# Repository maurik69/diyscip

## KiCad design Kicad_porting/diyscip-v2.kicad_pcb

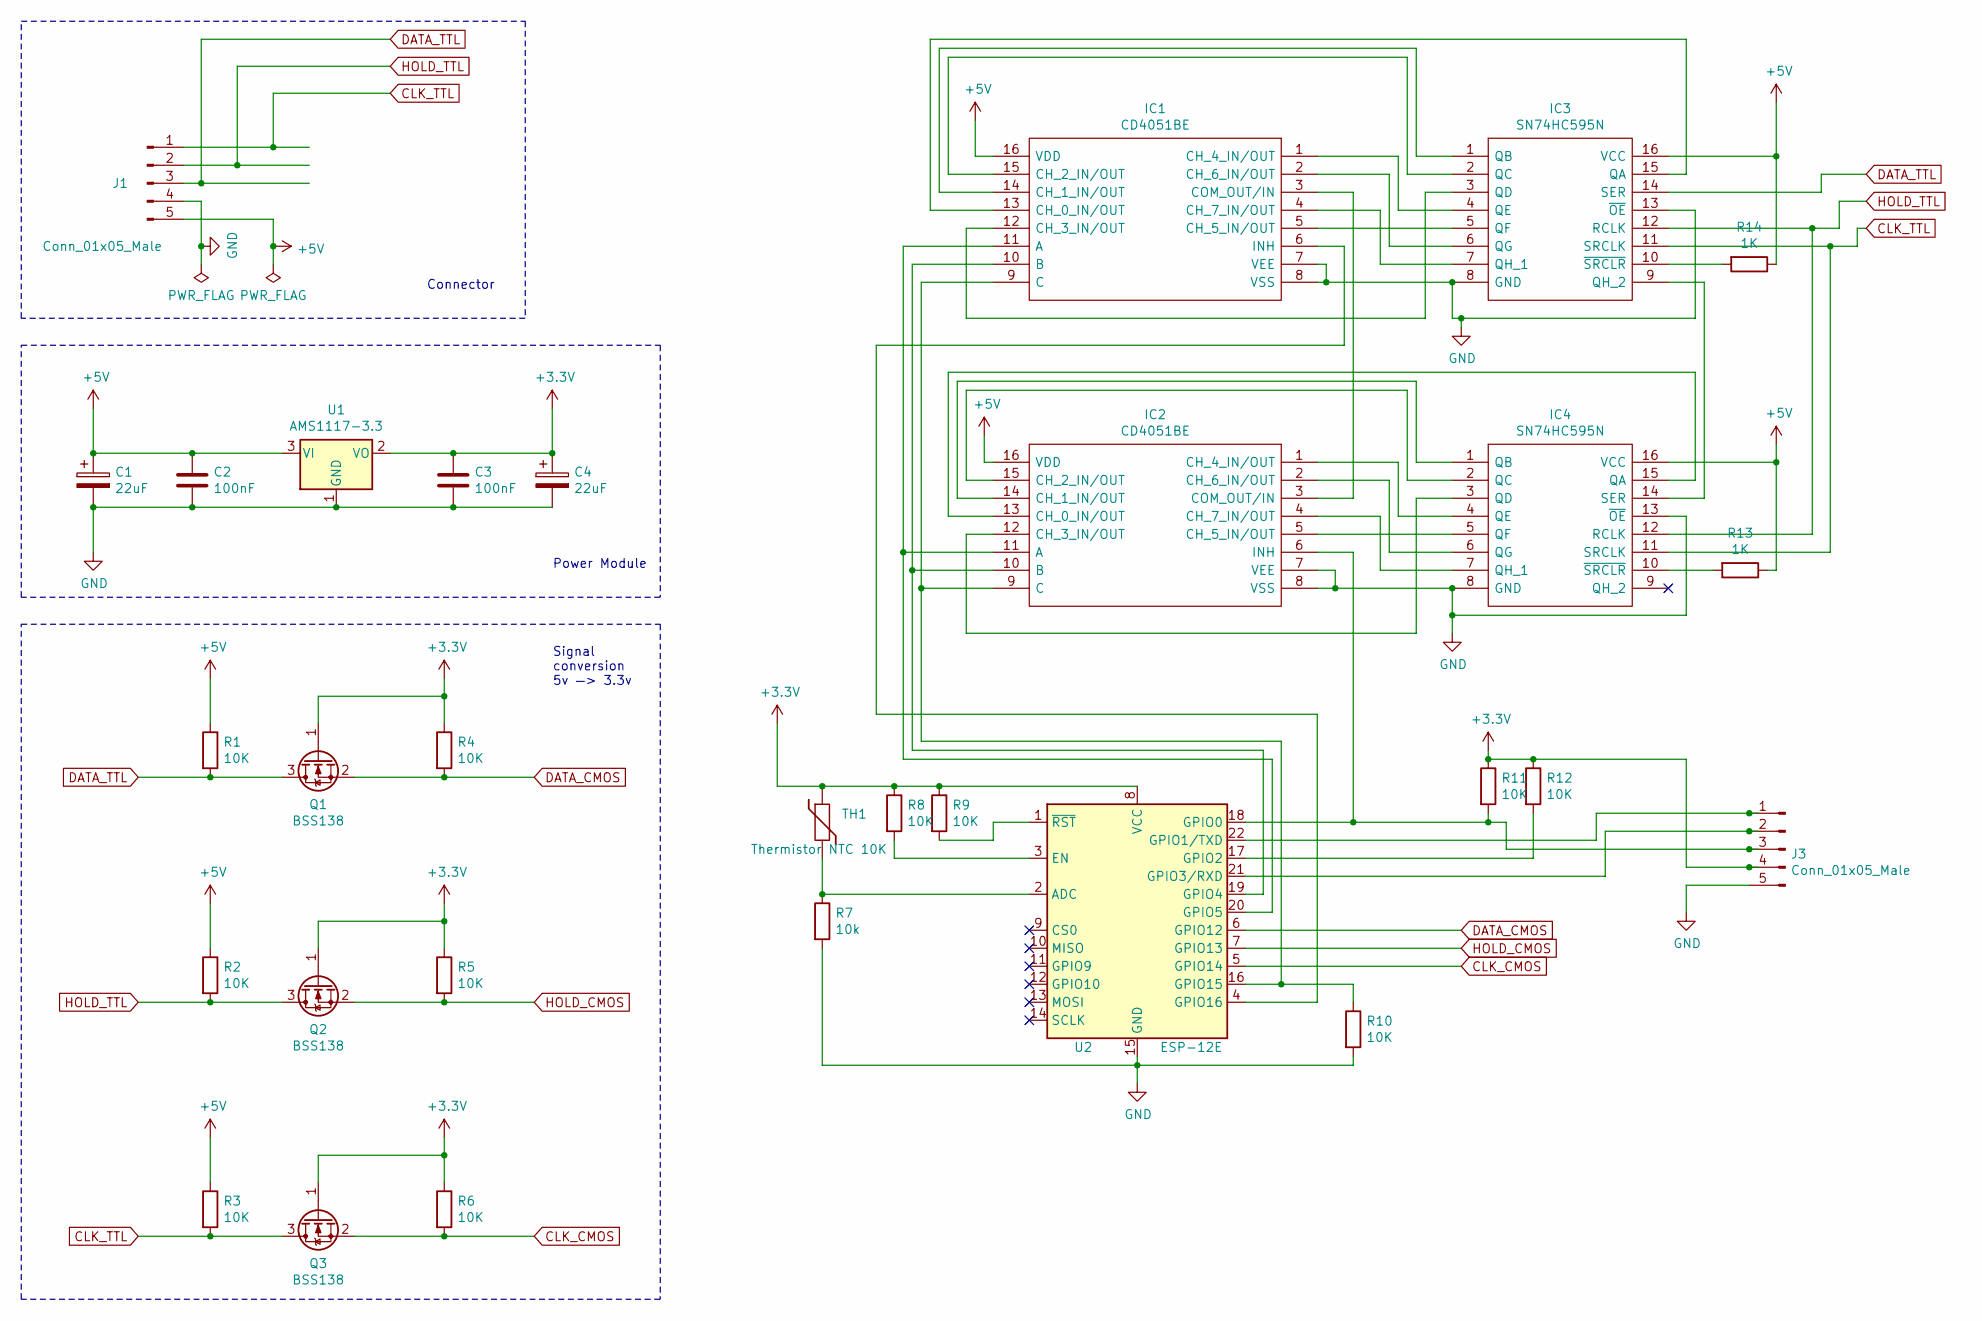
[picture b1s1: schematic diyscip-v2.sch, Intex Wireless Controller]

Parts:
C1, C4: 22uF; C_1206_3216Metric; LCSC C12891
C2, C3: 100nF; C_0603_1608Metric; LCSC C14663
IC1, IC2: CD4051BE; DIP794W53P254L1930H508Q16N; Mouser Part Number 595-CD4051BE
IC3, IC4: SN74HC595N; DIP794W53P254L1930H508Q16N; Mouser Part Number 595-SN74HC595N
J1: Conn_01x05_Male; JST_VH_B5P-VH-B_1x05_P3.96mm_Vertical
J3: Conn_01x05_Male; PinHeader_1x05_P2.54mm_Vertical
Q1, Q2, Q3: BSS138; SOT-23; LCSC C112239
R1, R2, R3, R4, R5, R6, R8, R9, R10, R11, R12: 10K; R_0603_1608Metric; LCSC C25804
R7: 10k; R_0603_1608Metric; LCSC C25804
R13, R14: 1K; R_0603_1608Metric; LCSC C21190
TH1: Thermistor NTC 10K; R_0603_1608Metric; LCSC C76589
U1: AMS1117-3.3; SOT-223-3_TabPin2; LCSC C6186
U2: ESP-12E; LCSC C82891

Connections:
+3V3: C3.1, C4.1, J3.4, Q1.1 (G), Q2.1 (G), Q3.1 (G), R4.1, R5.1, R6.1, R8.1, R9.1, R11.1, R12.1, TH1.1, U1.2 (VO), U2.8 (VCC)
+5V: C1.1, C2.1, IC1.16 (VDD), IC2.16 (VDD), IC3.16 (VCC), IC4.16 (VCC), J1.5, R1.1, R2.1, R3.1, R13.1, R14.1, U1.3 (VI)
CLK_CMOS: Q3.2 (S), R6.2, U2.5 (GPIO14)
CLK_TTL: IC3.11 (SRCLK), IC4.11 (SRCLK), J1.1, Q3.3 (D), R3.2
DATA_CMOS: Q1.2 (S), R4.2, U2.6 (GPIO12)
DATA_TTL: IC3.14 (SER), J1.3, Q1.3 (D), R1.2; also elsewhere on the board
GND: C1.2, C2.2, C3.2, C4.2, IC1.7 (VEE), IC1.8 (VSS), IC2.7 (VEE), IC2.8 (VSS), IC3.8 (GND), IC3.13 (~OE), IC4.8 (GND), IC4.13 (~OE), J1.4, J3.5, R7.2, R10.2, U1.1 (GND), U2.15 (GND)
HOLD_CMOS: Q2.2 (S), R5.2, U2.7 (GPIO13)
HOLD_TTL: IC3.12 (RCLK), IC4.12 (RCLK), J1.2, Q2.3 (D), R2.2
unnamed: IC1.1 (CH_4_IN/OUT), IC3.4 (QE)
unnamed: IC1.2 (CH_6_IN/OUT), IC3.6 (QG)
unnamed 11: IC1.3 (COM_OUT/IN), IC2.3 (COM_OUT/IN); also elsewhere on the board
unnamed: IC1.4 (CH_7_IN/OUT), IC3.7 (QH_1)
unnamed: IC1.5 (CH_5_IN/OUT), IC3.5 (QF)
unnamed: IC1.6 (INH), U2.4 (GPIO16)
unnamed: IC1.9 (C), IC2.9 (C), R10.1, U2.16 (GPIO15)
unnamed: IC1.10 (B), IC2.10 (B), U2.19 (GPIO4)
unnamed: IC1.11 (A), IC2.11 (A), U2.20 (GPIO5)
unnamed: IC1.12 (CH_3_IN/OUT), IC3.3 (QD)
unnamed: IC1.13 (CH_0_IN/OUT), IC3.15 (QA)
unnamed: IC1.14 (CH_1_IN/OUT), IC3.1 (QB)
unnamed: IC1.15 (CH_2_IN/OUT), IC3.2 (QC)
unnamed: IC2.1 (CH_4_IN/OUT), IC4.4 (QE)
unnamed: IC2.2 (CH_6_IN/OUT), IC4.6 (QG)
unnamed: IC2.4 (CH_7_IN/OUT), IC4.7 (QH_1)
unnamed: IC2.5 (CH_5_IN/OUT), IC4.5 (QF)
unnamed: IC2.6 (INH), J3.3, R11.2, U2.18 (GPIO0)
unnamed: IC2.12 (CH_3_IN/OUT), IC4.3 (QD)
unnamed: IC2.13 (CH_0_IN/OUT), IC4.15 (QA)
unnamed: IC2.14 (CH_1_IN/OUT), IC4.1 (QB)
unnamed: IC2.15 (CH_2_IN/OUT), IC4.2 (QC)
unnamed: IC3.9 (QH_2), IC4.14 (SER)
unnamed: IC3.10 (~SRCLR), R14.2
unnamed: IC4.10 (~SRCLR), R13.2
unnamed: J3.1, U2.22 (GPIO1/TXD)
unnamed: J3.2, U2.21 (GPIO3/RXD)
unnamed: R7.1, TH1.2, U2.2 (ADC)
unnamed: R8.2, U2.3 (EN)
unnamed: R9.2, U2.1 (~RST)
unnamed: R12.2, U2.17 (GPIO2)

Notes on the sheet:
Connector
Power Module
Signal conversion 5v —> 3.3v

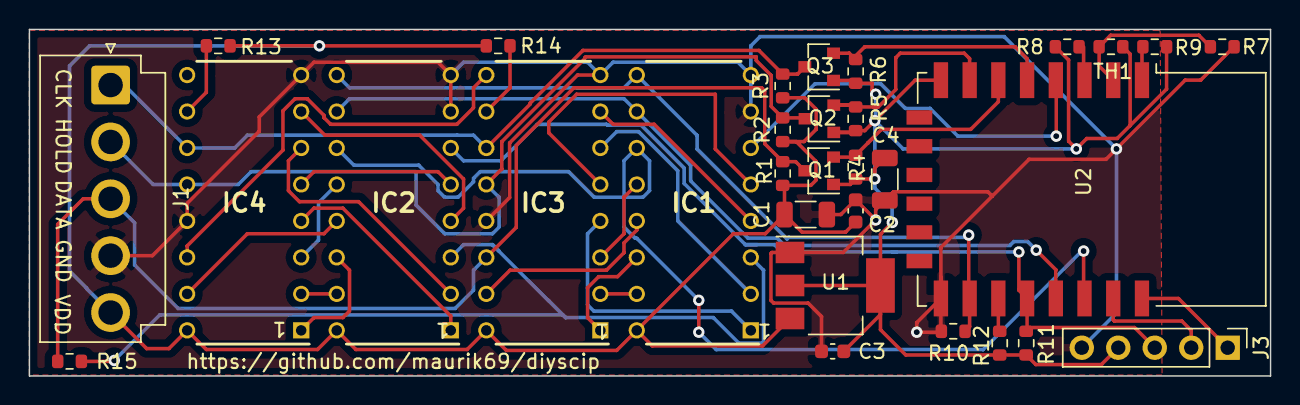
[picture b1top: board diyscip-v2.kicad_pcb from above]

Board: 2 copper layers, 86.4 x 24.1 mm, 31 parts (0 on the bottom side), 40 nets.

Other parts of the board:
R15: 1K; R_0603_1608Metric

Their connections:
DATA_TTL: R15.1; also elsewhere on the board
unnamed 11: R15.2; also elsewhere on the board

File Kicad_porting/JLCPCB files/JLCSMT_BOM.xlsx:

Comment | Designator | Footprint | LCSC Part #（optional）
22uF | C1,C4 | Capacitor_SMD:C_1206_3216Metric | C12891
100nF | C2,C3 | Capacitor_SMD:C_0603_1608Metric | C14663
CD4051BE | IC1,IC2 | SamacSys_Parts:DIP794W53P254L1930H508Q16N
SN74HC595N | IC3,IC4 | SamacSys_Parts:DIP794W53P254L1930H508Q16N
Conn_01x05_Male | J1 | Connector_JST:JST_VH_B5P-VH-B_1x05_P3.96mm_Vertical
Conn_01x05_Male | J3 | Connector_PinHeader_2.54mm:PinHeader_1x05_P2.54mm_Vertical
BSS138 | Q1,Q2,Q3 | Package_TO_SOT_SMD:SOT-23 | C112239
10K | R1,R2,R3,R4,R5,R6,R8,R9,R10,R11,R12 | Resistor_SMD:R_0603_1608Metric | C25804
1K | R13,R14 | Resistor_SMD:R_0603_1608Metric | C21190
10k | R7 | Resistor_SMD:R_0603_1608Metric | C25804
Thermistor NTC 10K | TH1 | Resistor_SMD:R_0603_1608Metric | C76589
AMS1117-3.3 | U1 | Package_TO_SOT_SMD:SOT-223-3_TabPin2 | C6186
ESP-12E | U2 | RF_Module:ESP-12E | C82891

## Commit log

2021-01-02 Kicad porting with JLCPCB files to order new boards
2021-01-02 gerber with thermal copper
2021-01-02 Setting for serial flashing: "pio run -t upload"
2021-01-15 Correzione errore scritta connettore programmazione.
2021-01-22 Aggiunta resistenza "dimenticata" su segnale DATA
